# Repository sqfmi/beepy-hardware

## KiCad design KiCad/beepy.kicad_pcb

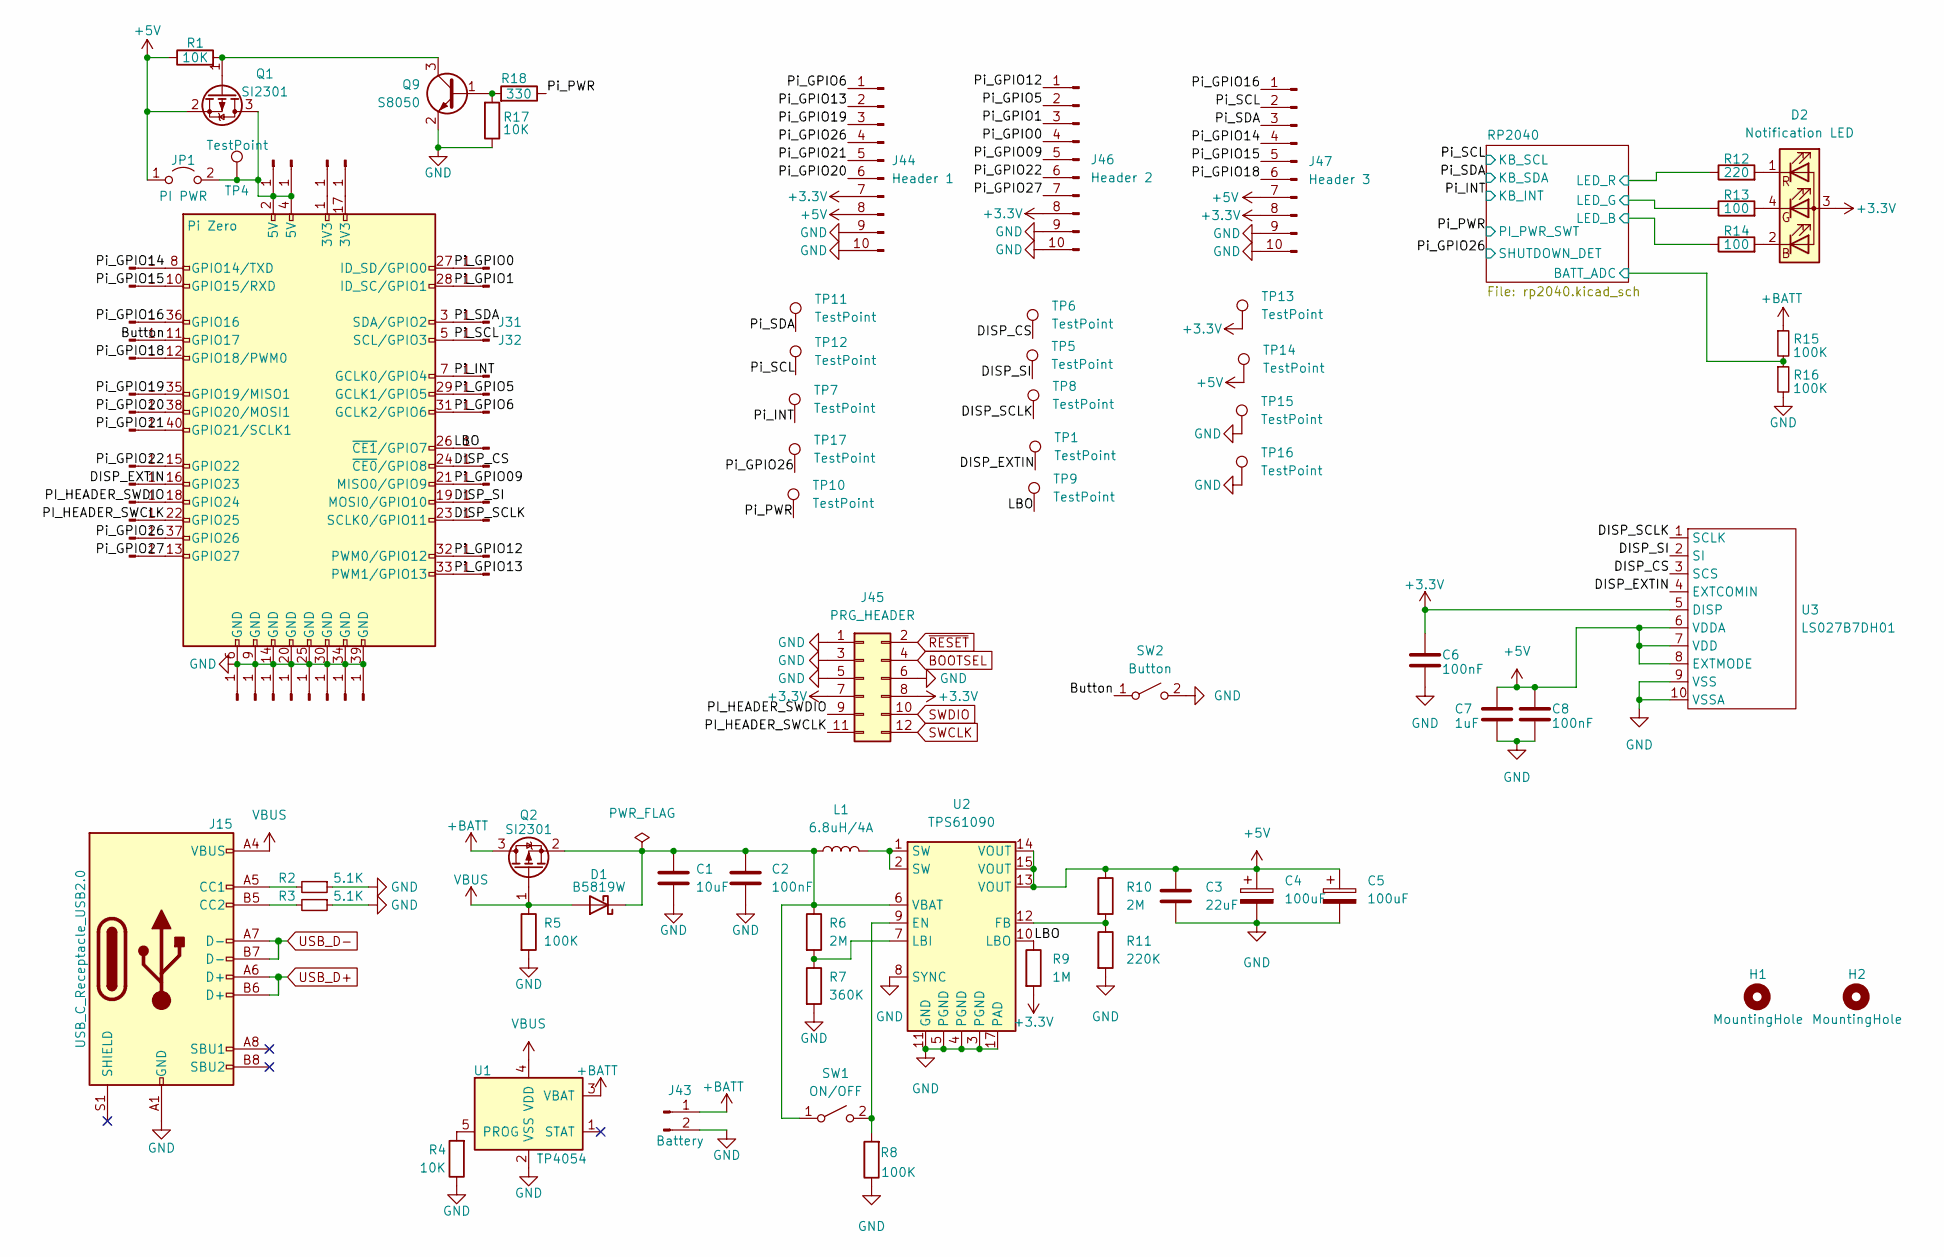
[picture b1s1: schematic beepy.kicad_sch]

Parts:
C1: 10uF; C_0603_1608Metric
C2, C6, C8: 100nF; C_0603_1608Metric
C3: 22uF; C_1206_3216Metric
C4, C5: 100uF; CP_EIA-3528-15_AVX-H
C7: 1uF; C_0603_1608Metric
D1: B5819W; D_SOD-123
D2: Notification LED; FM-B2020RGBA-HG
H1, H2: MountingHole; MountingHole_2.7mm_M2.5
J1, J2, J3, J4, J5, J6, J7, J8, J9, J10, J11, J12, J13, J14, J16, J17, J18, J19, J20, J21, J23, J24, J25, J26, J27, J28, J29, J30, J31, J32, J33, J34, J35, J36, J37, J38, J39, J40, J41, J42: FDX0019B1
J15: USB_C_Receptacle_USB2.0; USB_C_Receptacle_HRO_TYPE-C-31-M-12; LCSC C165948
J22: Pi Zero; Raspberry_Pi_Zero_Socketed_SMD_FaceUP_MountingHoles
J43: Battery; JST_PH_S2B-PH-SM4-TB_1x02-1MP_P2.00mm_Horizontal
J44: Header 1; PinHeader_1x10_P2.54mm_Vertical
J45: PRG_HEADER; PinHeader_2x06_P1.27mm_Vertical_SMD
J46: Header 2; PinHeader_1x10_P2.54mm_Vertical
J47: Header 3; PinHeader_1x10_P2.54mm_Vertical
JP1: PI PWR; SolderJumper-2_P1.3mm_Open_RoundedPad1.0x1.5mm
L1: 6.8uH/4A; L_Bourns_SRP7028A_7.3x6.6mm
Q1, Q2: SI2301; SOT-23
Q9: S8050; SOT-23
R1, R4, R17: 10K; R_0603_1608Metric
R2, R3: 5.1K; R_0603_1608Metric
R5, R8, R15, R16: 100K; R_0603_1608Metric
R6, R10: 2M; R_0603_1608Metric
R7: 360K; R_0603_1608Metric
R9: 1M; R_0603_1608Metric
R11: 220K; R_0603_1608Metric
R12: 220; R_0603_1608Metric
R13, R14: 100; R_0603_1608Metric
R18: 330; R_0603_1608Metric
SW1: ON/OFF; SW_SPDT_PCM12
SW2: Button; Panasonic_EVQPUL_EVQPUC
TP1, TP4, TP5, TP6, TP7, TP8, TP9, TP10, TP11, TP12, TP13, TP14, TP15, TP16, TP17: TestPoint; TestPoint_Pad_D1.5mm
U1: TP4054; SOT-23-5
U2: TPS61090; HTSSOP-16-1EP_4.4x5mm_P0.65mm_EP3.4x5mm_Mask2.46x2.31mm_The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
U3: LS027B7DH01; HRS_FH34SRJ-10S-0.5SH(50)

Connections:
+3V3: C6.1, D2.3 (A), J44.7, J45.7, J45.8, J46.8, J47.8, R9.2, TP13.1, U3.5 (DISP); also elsewhere on the board
+5V: C3.1, C4.1, C5.1, C7.1, C8.1, J44.8, J47.7, JP1.1 (A), Q1.2 (S), R1.1, R10.1, TP14.1, U2.13 (VOUT), U2.14 (VOUT), U2.15 (VOUT), U3.6 (VDDA), U3.7 (VDD), U3.8 (EXTMODE); also elsewhere on the board
+BATT: J43.1, Q2.3 (D), R15.1, U1.3 (VBAT)
/Button: J4.1, J22.11 (GPIO17), SW2.1 (A)
/DISP_CS: J22.24 (~CE0/GPIO8), J37.1, TP6.1, U3.3 (SCS)
/DISP_EXTIN: J10.1, J22.16 (GPIO23), TP1.1, U3.4 (EXTCOMIN)
/DISP_SCLK: J22.23 (SCLK0/GPIO11), J40.1, TP8.1, U3.1 (SCLK)
/DISP_SI: J22.19 (MOSI0/GPIO10), J39.1, TP5.1, U3.2 (SI)
/LBO: J22.26 (~CE1/GPIO7), J36.1, R9.1, TP9.1, U2.10 (LBO)
/PI_HEADER_SWCLK: J12.1, J22.22 (GPIO25), J45.11
/PI_HEADER_SWDIO: J11.1, J22.18 (GPIO24), J45.9
/Pi_GPIO0: J22.27 (ID_SD/GPIO0), J29.1, J46.4
/Pi_GPIO1: J22.28 (ID_SC/GPIO1), J30.1, J46.3
/Pi_GPIO5: J22.29 (GCLK1/GPIO5), J34.1, J46.2
/Pi_GPIO6: J22.31 (GCLK2/GPIO6), J35.1, J44.1
/Pi_GPIO09: J22.21 (MISO0/GPIO9), J38.1, J46.5
/Pi_GPIO12: J22.32 (PWM0/GPIO12), J41.1, J46.1
/Pi_GPIO13: J22.33 (PWM1/GPIO13), J42.1, J44.2
/Pi_GPIO14: J1.1, J22.8 (GPIO14/TXD), J47.4
/Pi_GPIO15: J2.1, J22.10 (GPIO15/RXD), J47.5
/Pi_GPIO16: J3.1, J22.36 (GPIO16), J47.1
/Pi_GPIO18: J5.1, J22.12 (GPIO18/PWM0), J47.6
/Pi_GPIO19: J6.1, J22.35 (GPIO19/MISO1), J44.3
/Pi_GPIO20: J7.1, J22.38 (GPIO20/MOSI1), J44.6
/Pi_GPIO21: J8.1, J22.40 (GPIO21/SCLK1), J44.5
/Pi_GPIO22: J9.1, J22.15 (GPIO22), J46.6
/Pi_GPIO26: J13.1, J22.37 (GPIO26), J44.4, TP17.1; also elsewhere on the board
/Pi_GPIO27: J14.1, J22.13 (GPIO27), J46.7
/Pi_INT: J22.7 (GCLK0/GPIO4), J33.1, TP7.1; also elsewhere on the board
/Pi_PWR: R18.1, TP10.1; also elsewhere on the board
/Pi_SCL: J22.5 (SCL/GPIO3), J32.1, J47.2, TP12.1; also elsewhere on the board
/Pi_SDA: J22.3 (SDA/GPIO2), J31.1, J47.3, TP11.1; also elsewhere on the board
/keyboard/BATT_ADC: R15.2, R16.1; also elsewhere on the board
/keyboard/LED_B: R14.1; also elsewhere on the board
/keyboard/LED_G: R13.1; also elsewhere on the board
/keyboard/LED_R: R12.1; also elsewhere on the board
BOOTSEL: J45.4; also elsewhere on the board
GND: C1.2, C2.2, C3.2, C4.2, C5.2, C6.2, C7.2, C8.2, J15.A1 (GND), J15.A12 (GND), J15.B1 (GND), J15.B12 (GND), J16.1, J17.1, J19.1, J21.1, J22.6 (GND), J22.9 (GND), J22.14 (GND), J22.20 (GND), J22.25 (GND), J22.30 (GND), J22.34 (GND), J22.39 (GND), J23.1, J25.1, J27.1, J28.1, J43.2, J44.9, J44.10, J45.1, J45.3, J45.5, J45.6, J46.9, J46.10, J47.9, J47.10, Q9.2 (E), R2.1, R3.1, R4.1, R5.2, R7.2, R8.1, R11.2, R16.2, R17.1, SW2.2 (B), TP15.1, TP16.1, U1.2 (VSS), U2.3 (PGND), U2.4 (PGND), U2.5 (PGND), U2.8 (SYNC), U2.11 (GND), U2.17 (PAD), U3.9 (VSS), U3.10 (VSSA); also elsewhere on the board
unnamed: C1.1, C2.1, D1.1 (K), L1.1, Q2.2 (S), R6.1, SW1.1 (A), U2.6 (VBAT)
unnamed: D2.1 (RK), R12.2
unnamed: D2.2 (BK), R14.2
unnamed: D2.4 (GK), R13.2
unnamed: J15.A5 (CC1), R2.2
unnamed: J15.B5 (CC2), R3.2
unnamed: J18.1, J20.1, J22.2 (5V), J22.4 (5V), JP1.2 (B), Q1.3 (D), TP4.1
unnamed: J22.1 (3V3), J24.1
unnamed: J22.17 (3V3), J26.1
unnamed: L1.2, U2.1 (SW), U2.2 (SW)
unnamed: Q1.1 (G), Q9.3 (C), R1.2
unnamed: Q9.1 (B), R17.2, R18.2
unnamed: R4.2, U1.5 (PROG)
unnamed: R6.2, R7.1, U2.7 (LBI)
unnamed: R8.2, SW1.2 (B), U2.9 (EN)
unnamed: R10.2, R11.1, U2.12 (FB)
SWCLK: J45.12; also elsewhere on the board
SWDIO: J45.10; also elsewhere on the board
USB_D+: J15.A6 (D+), J15.B6 (D+); also elsewhere on the board
USB_D-: J15.A7 (D-), J15.B7 (D-); also elsewhere on the board
VBUS: D1.2 (A), J15.A4 (VBUS), J15.A9 (VBUS), J15.B4 (VBUS), J15.B9 (VBUS), Q2.1 (G), R5.1, U1.4 (VDD)
~RESET: J45.2; also elsewhere on the board

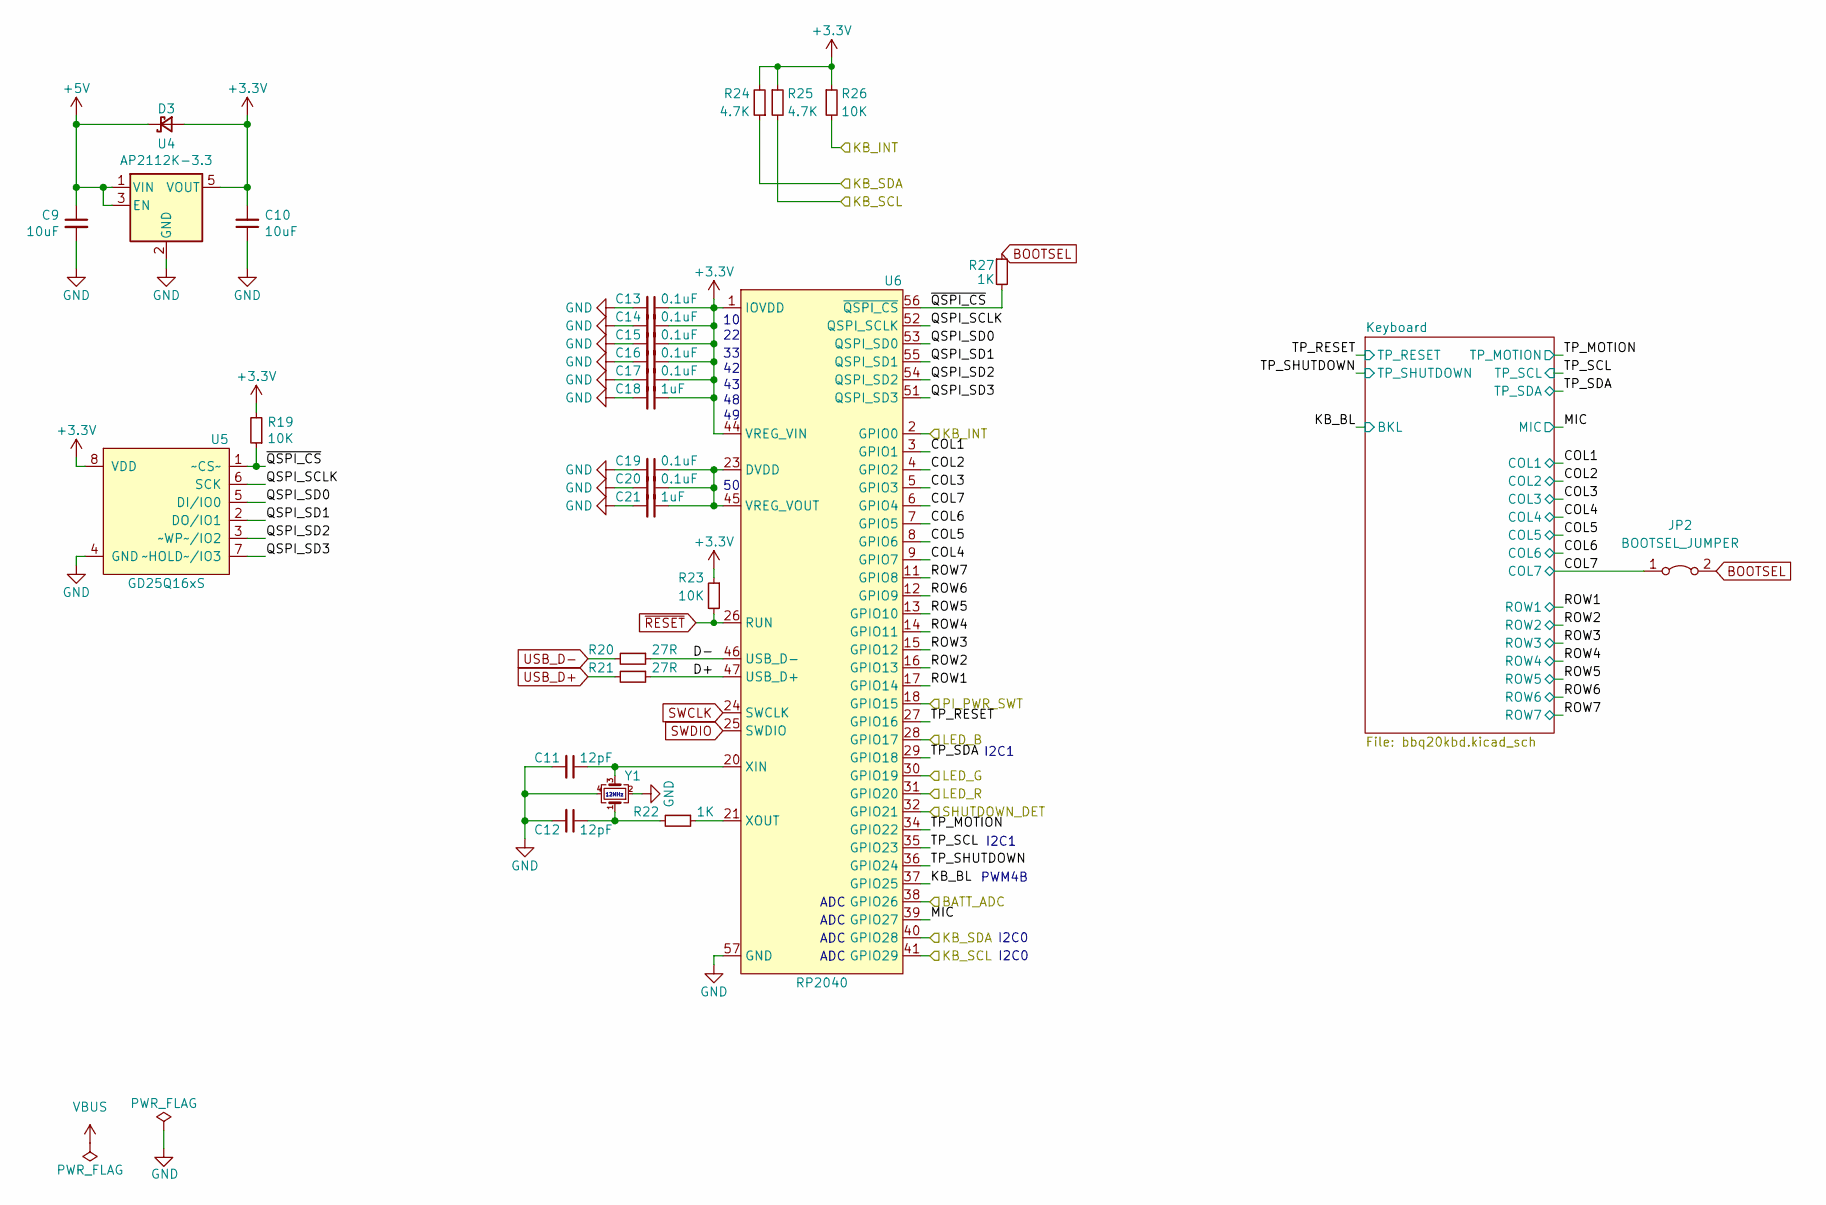
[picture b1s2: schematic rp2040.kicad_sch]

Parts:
C9, C10: 10uF; C_0603_1608Metric
C11, C12: 12pF; C_0603_1608Metric
C13, C14, C15, C16, C17, C19, C20: 0.1uF; C_0603_1608Metric
C18, C21: 1uF; C_0603_1608Metric
D3: D_Schottky_Small; D_SOD-323; LCSC C114023
JP2: BOOTSEL_JUMPER; SolderJumper-2_P1.3mm_Bridged_RoundedPad1.0x1.5mm
R19, R23, R26: 10K; R_0603_1608Metric
R20, R21: 27R; R_0603_1608Metric
R22, R27: 1K; R_0603_1608Metric
R24, R25: 4.7K; R_0603_1608Metric
U4: AP2112K-3.3; SOT-23-5; LCSC C51118
U5: GD25Q16xS; SSOP-8_5.25x5.24mm_P1.27mm; LCSC C79074
U6: RP2040; QFN-56-1EP_7x7mm_P0.4mm_EP5.6x5.6mm
Y1: XYDBPCNANF-12MHZ; Crystal_SMD_3225-4Pin_3.2x2.5mm; LCSC C709001

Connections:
+3V3: C10.2, C13.1, C14.1, C15.1, C16.1, C17.1, C18.1, D3.2 (A), R19.2, R23.1, R24.2, R25.1, R26.1, U4.5 (VOUT), U5.8 (VDD), U6.1 (IOVDD), U6.10 (IOVDD), U6.22 (IOVDD), U6.33 (IOVDD), U6.42 (IOVDD), U6.43 (ADC_AVDD), U6.44 (VREG_VIN), U6.48 (USB_VDD), U6.49 (IOVDD); also elsewhere on the board
+5V: C9.1, D3.1 (K), U4.1 (VIN), U4.3 (EN); also elsewhere on the board
/Pi_GPIO26: U6.32 (GPIO21); also elsewhere on the board
/Pi_INT: R26.2, U6.2 (GPIO0); also elsewhere on the board
/Pi_PWR: U6.18 (GPIO15); also elsewhere on the board
/Pi_SCL: R25.2, U6.41 (GPIO29); also elsewhere on the board
/Pi_SDA: R24.1, U6.40 (GPIO28); also elsewhere on the board
/keyboard/BATT_ADC: U6.38 (GPIO26); also elsewhere on the board
/keyboard/COL1: U6.3 (GPIO1); also elsewhere on the board
/keyboard/COL2: U6.4 (GPIO2); also elsewhere on the board
/keyboard/COL3: U6.5 (GPIO3); also elsewhere on the board
/keyboard/COL4: U6.9 (GPIO7); also elsewhere on the board
/keyboard/COL5: U6.8 (GPIO6); also elsewhere on the board
/keyboard/COL6: U6.7 (GPIO5); also elsewhere on the board
/keyboard/COL7: JP2.1 (A), U6.6 (GPIO4); also elsewhere on the board
/keyboard/D+: R21.1, U6.47 (USB_D+)
/keyboard/D-: R20.1, U6.46 (USB_D-)
/keyboard/KB_BL: U6.37 (GPIO25); also elsewhere on the board
/keyboard/LED_B: U6.28 (GPIO17); also elsewhere on the board
/keyboard/LED_G: U6.30 (GPIO19); also elsewhere on the board
/keyboard/LED_R: U6.31 (GPIO20); also elsewhere on the board
/keyboard/MIC: U6.39 (GPIO27); also elsewhere on the board
/keyboard/QSPI_SCLK: U5.6 (SCK), U6.52 (QSPI_SCLK)
/keyboard/QSPI_SD0: U5.5 (DI/IO0), U6.53 (QSPI_SD0)
/keyboard/QSPI_SD1: U5.2 (DO/IO1), U6.55 (QSPI_SD1)
/keyboard/QSPI_SD2: U5.3 (~WP~/IO2), U6.54 (QSPI_SD2)
/keyboard/QSPI_SD3: U5.7 (~HOLD~/IO3), U6.51 (QSPI_SD3)
/keyboard/ROW1: U6.17 (GPIO14); also elsewhere on the board
/keyboard/ROW2: U6.16 (GPIO13); also elsewhere on the board
/keyboard/ROW3: U6.15 (GPIO12); also elsewhere on the board
/keyboard/ROW4: U6.14 (GPIO11); also elsewhere on the board
/keyboard/ROW5: U6.13 (GPIO10); also elsewhere on the board
/keyboard/ROW6: U6.12 (GPIO9); also elsewhere on the board
/keyboard/ROW7: U6.11 (GPIO8); also elsewhere on the board
/keyboard/TP_MOTION: U6.34 (GPIO22); also elsewhere on the board
/keyboard/TP_RESET: U6.27 (GPIO16); also elsewhere on the board
/keyboard/TP_SCL: U6.35 (GPIO23); also elsewhere on the board
/keyboard/TP_SDA: U6.29 (GPIO18); also elsewhere on the board
/keyboard/TP_SHUTDOWN: U6.36 (GPIO24); also elsewhere on the board
/keyboard/~QSPI_CS: R19.1, R27.2, U5.1 (~CS~), U6.56 (~QSPI_CS)
BOOTSEL: JP2.2 (B), R27.1; also elsewhere on the board
GND: C9.2, C10.1, C11.2, C12.2, C13.2, C14.2, C15.2, C16.2, C17.2, C18.2, C19.2, C20.2, C21.2, U4.2 (GND), U5.4 (GND), U5.9 (GND), U6.19 (TESTEN), U6.57 (GND), Y1.2, Y1.4; also elsewhere on the board
unnamed: C11.1, U6.20 (XIN), Y1.3
unnamed: C12.1, R22.2, Y1.1
unnamed: C19.1, C20.1, C21.1, U6.23 (DVDD), U6.45 (VREG_VOUT), U6.50 (DVDD)
unnamed: R22.1, U6.21 (XOUT)
SWCLK: U6.24 (SWCLK); also elsewhere on the board
SWDIO: U6.25 (SWDIO); also elsewhere on the board
USB_D+: R21.2; also elsewhere on the board
USB_D-: R20.2; also elsewhere on the board
~RESET: R23.2, U6.26 (RUN); also elsewhere on the board

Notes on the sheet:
I2C0
I2C1
PWM4B
ADC
12MHz

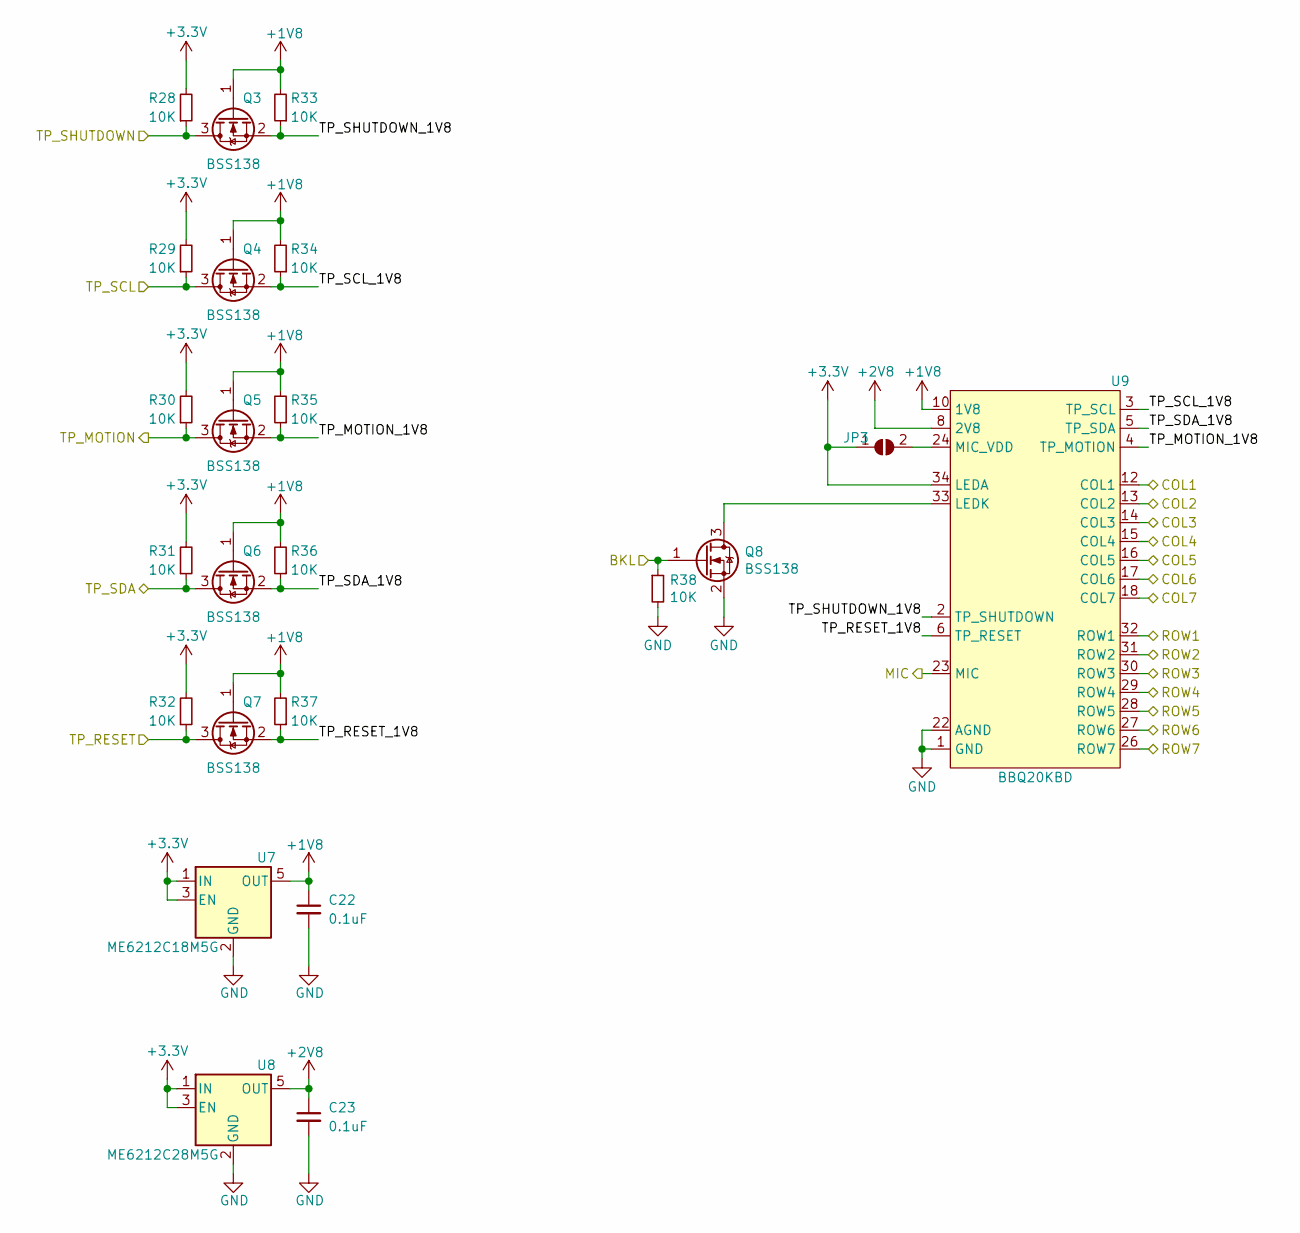
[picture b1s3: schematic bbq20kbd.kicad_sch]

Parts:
C22, C23: 0.1uF; C_0603_1608Metric
JP3: SJ_MIC_VDD; SolderJumper-2_P1.3mm_Open_RoundedPad1.0x1.5mm
Q3, Q4, Q5, Q6, Q7, Q8: BSS138; SOT-23; LCSC C112239
R28, R29, R30, R31, R32, R33, R34, R35, R36, R37, R38: 10K; R_0603_1608Metric
U7: ME6212C18M5G; SOT-23-5; LCSC C236669
U8: ME6212C28M5G; SOT-23-5; LCSC C427596
U9: BBQ20KBD; BM20B(0.8)-40DS-0.4V; LCSC C424543

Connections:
+1V8: C22.1, Q3.1 (G), Q4.1 (G), Q5.1 (G), Q6.1 (G), Q7.1 (G), R33.2, R34.2, R35.2, R36.2, R37.2, U7.5 (OUT), U9.10 (1V8)
+2V8: C23.1, U8.5 (OUT), U9.8 (2V8)
+3V3: JP3.1 (A), R28.2, R29.2, R30.2, R31.2, R32.2, U7.1 (IN), U7.3 (EN), U8.1 (IN), U8.3 (EN), U9.34 (LEDA), U9.36 (LEDA); also elsewhere on the board
/keyboard/COL1: U9.12 (COL1); also elsewhere on the board
/keyboard/COL2: U9.13 (COL2); also elsewhere on the board
/keyboard/COL3: U9.14 (COL3); also elsewhere on the board
/keyboard/COL4: U9.15 (COL4); also elsewhere on the board
/keyboard/COL5: U9.16 (COL5); also elsewhere on the board
/keyboard/COL6: U9.17 (COL6); also elsewhere on the board
/keyboard/COL7: U9.18 (COL7); also elsewhere on the board
/keyboard/KB_BL: Q8.1 (G), R38.1; also elsewhere on the board
/keyboard/Keyboard/TP_MOTION_1V8: Q5.2 (S), R35.1, U9.4 (TP_MOTION)
/keyboard/Keyboard/TP_RESET_1V8: Q7.2 (S), R37.1, U9.6 (TP_RESET)
/keyboard/Keyboard/TP_SCL_1V8: Q4.2 (S), R34.1, U9.3 (TP_SCL)
/keyboard/Keyboard/TP_SDA_1V8: Q6.2 (S), R36.1, U9.5 (TP_SDA)
/keyboard/Keyboard/TP_SHUTDOWN_1V8: Q3.2 (S), R33.1, U9.2 (TP_SHUTDOWN)
/keyboard/MIC: U9.23 (MIC); also elsewhere on the board
/keyboard/ROW1: U9.32 (ROW1); also elsewhere on the board
/keyboard/ROW2: U9.31 (ROW2); also elsewhere on the board
/keyboard/ROW3: U9.30 (ROW3); also elsewhere on the board
/keyboard/ROW4: U9.29 (ROW4); also elsewhere on the board
/keyboard/ROW5: U9.28 (ROW5); also elsewhere on the board
/keyboard/ROW6: U9.27 (ROW6); also elsewhere on the board
/keyboard/ROW7: U9.26 (ROW7); also elsewhere on the board
/keyboard/TP_MOTION: Q5.3 (D), R30.1; also elsewhere on the board
/keyboard/TP_RESET: Q7.3 (D), R32.1; also elsewhere on the board
/keyboard/TP_SCL: Q4.3 (D), R29.1; also elsewhere on the board
/keyboard/TP_SDA: Q6.3 (D), R31.1; also elsewhere on the board
/keyboard/TP_SHUTDOWN: Q3.3 (D), R28.1; also elsewhere on the board
GND: C22.2, C23.2, Q8.2 (S), R38.2, U7.2 (GND), U8.2 (GND), U9.1 (GND), U9.7 (GND), U9.9 (GND), U9.11 (GND), U9.19 (GND), U9.20 (GND), U9.21 (GND), U9.22 (AGND), U9.25 (GND), U9.40 (GND); also elsewhere on the board
unnamed: JP3.2 (B), U9.24 (MIC_VDD)
unnamed: Q8.3 (D), U9.33 (LEDK), U9.35 (LEDK), U9.37 (LEDK)

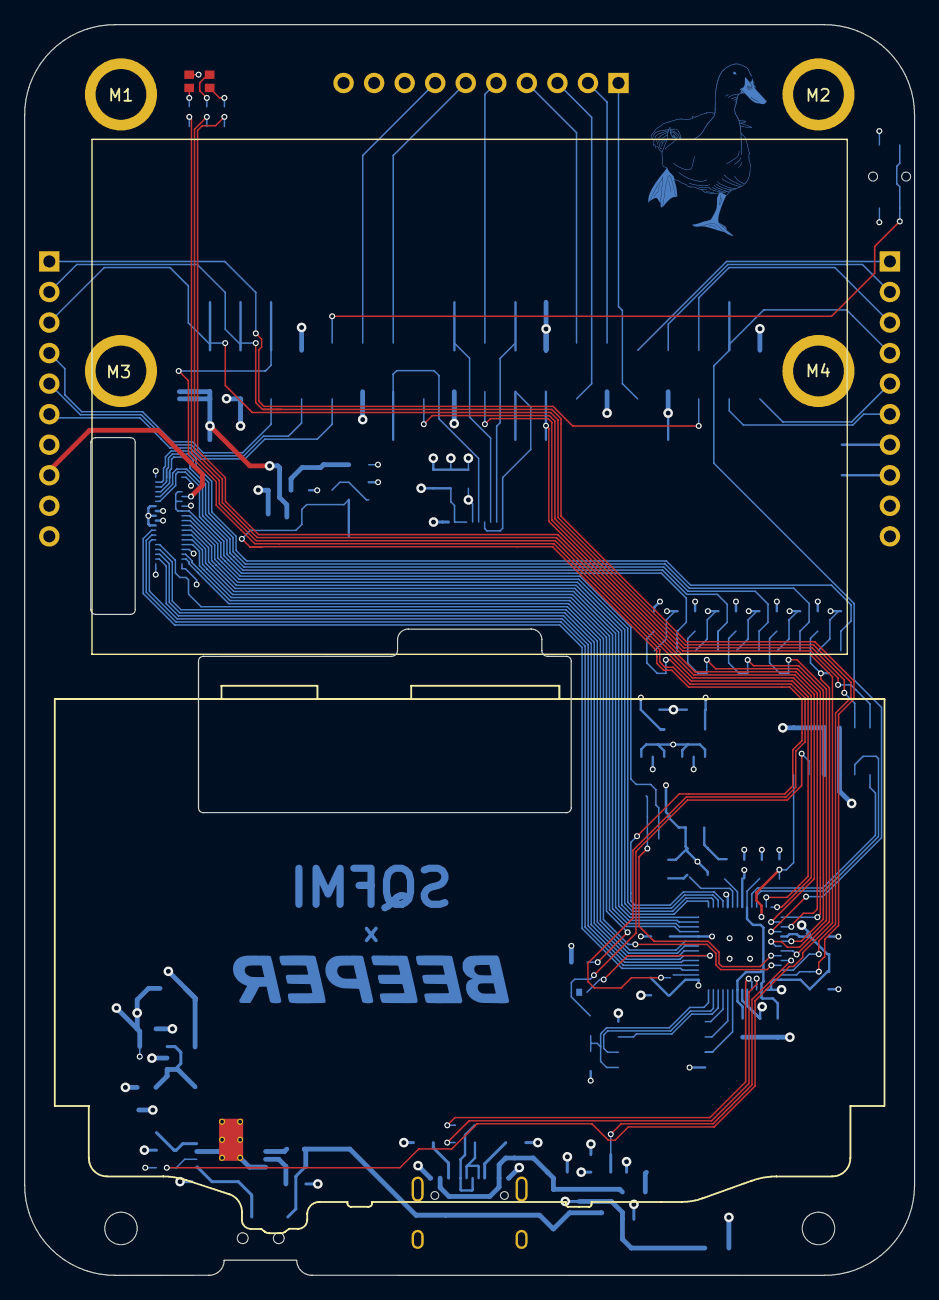
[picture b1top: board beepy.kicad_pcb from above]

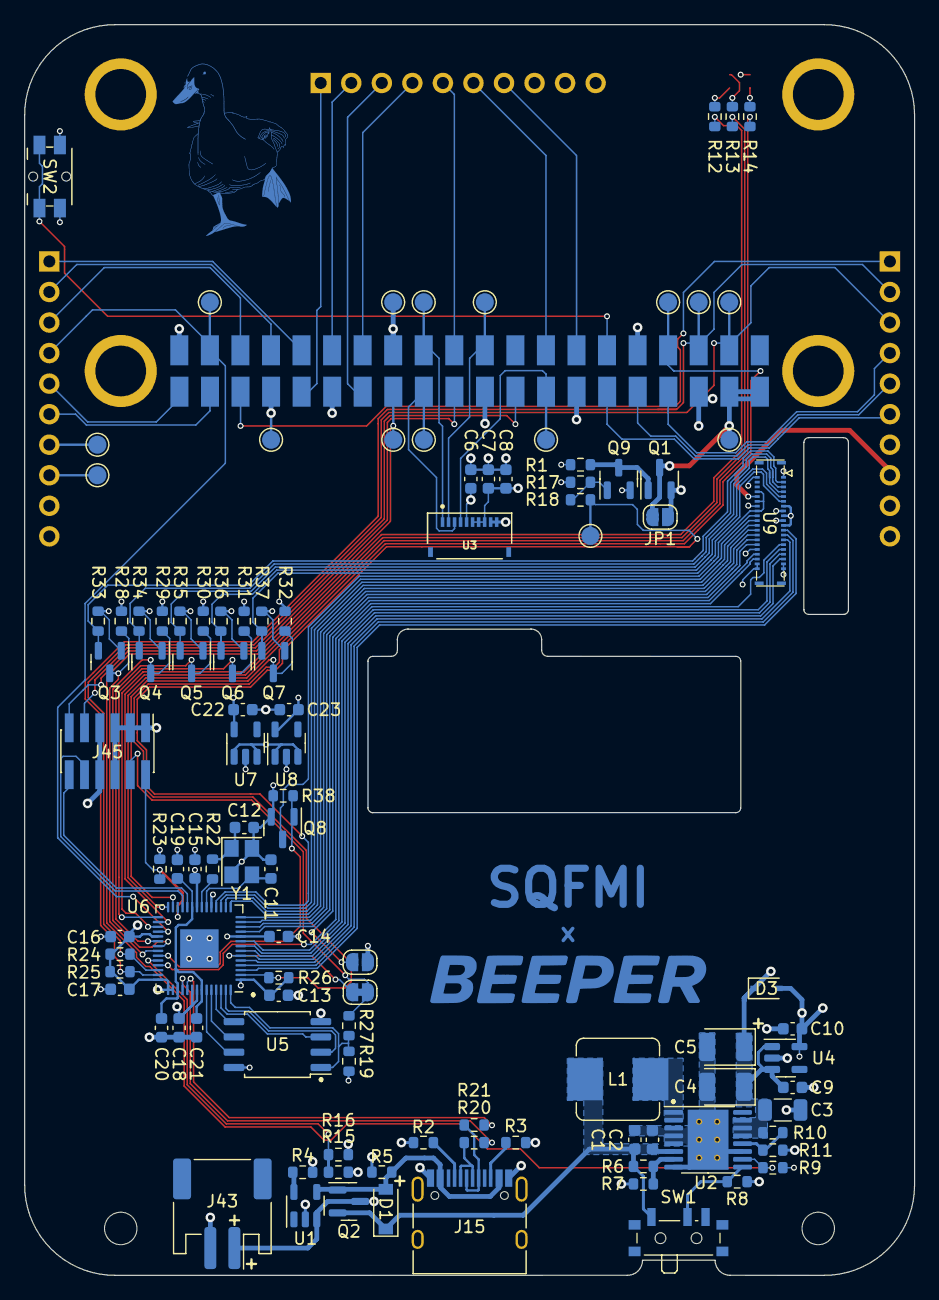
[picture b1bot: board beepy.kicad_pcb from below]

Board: 4 copper layers, 74.0 x 104.0 mm, 157 parts (154 on the bottom side), 100 nets.

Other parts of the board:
M1, M2, M3, M4: MountingHole_2.5mm_Pad
REFe: SQFMI-DUCK-LOGO; SQFMI-DUCK-LOGO-BCU

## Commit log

2023-06-08 adding KiCad files
2023-06-08 add v1 case step
2023-06-09 adding models and images
2023-06-09 Add cad link
2023-06-09 Add step files
2023-06-10 added rev6 models
2023-08-14 feat: add slide cover stl with readme
2023-08-16 update files

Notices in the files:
KiCad/bbq20kbd.kicad_sch:
CERN Open Hardware Licence v1.2
